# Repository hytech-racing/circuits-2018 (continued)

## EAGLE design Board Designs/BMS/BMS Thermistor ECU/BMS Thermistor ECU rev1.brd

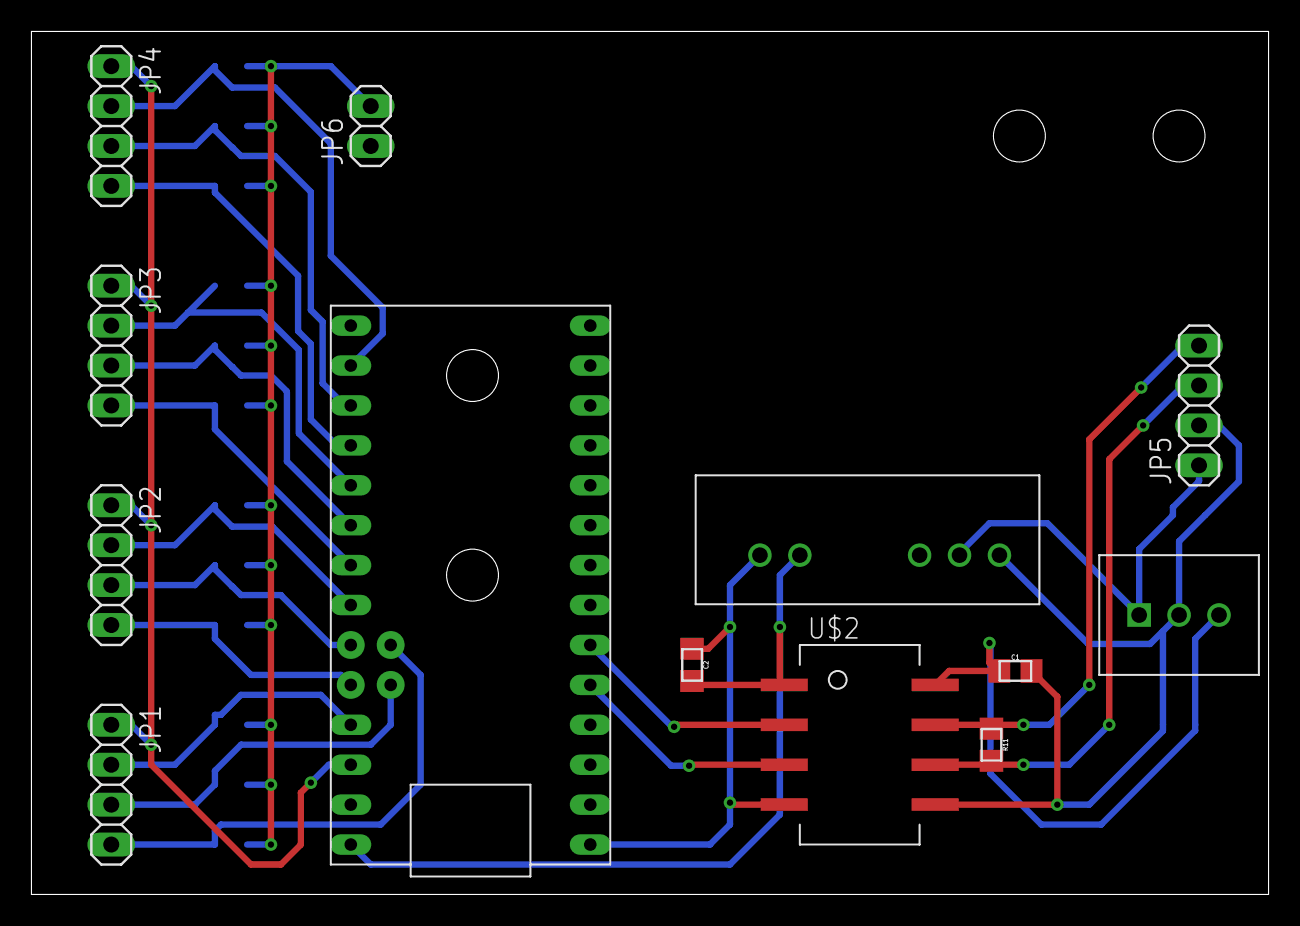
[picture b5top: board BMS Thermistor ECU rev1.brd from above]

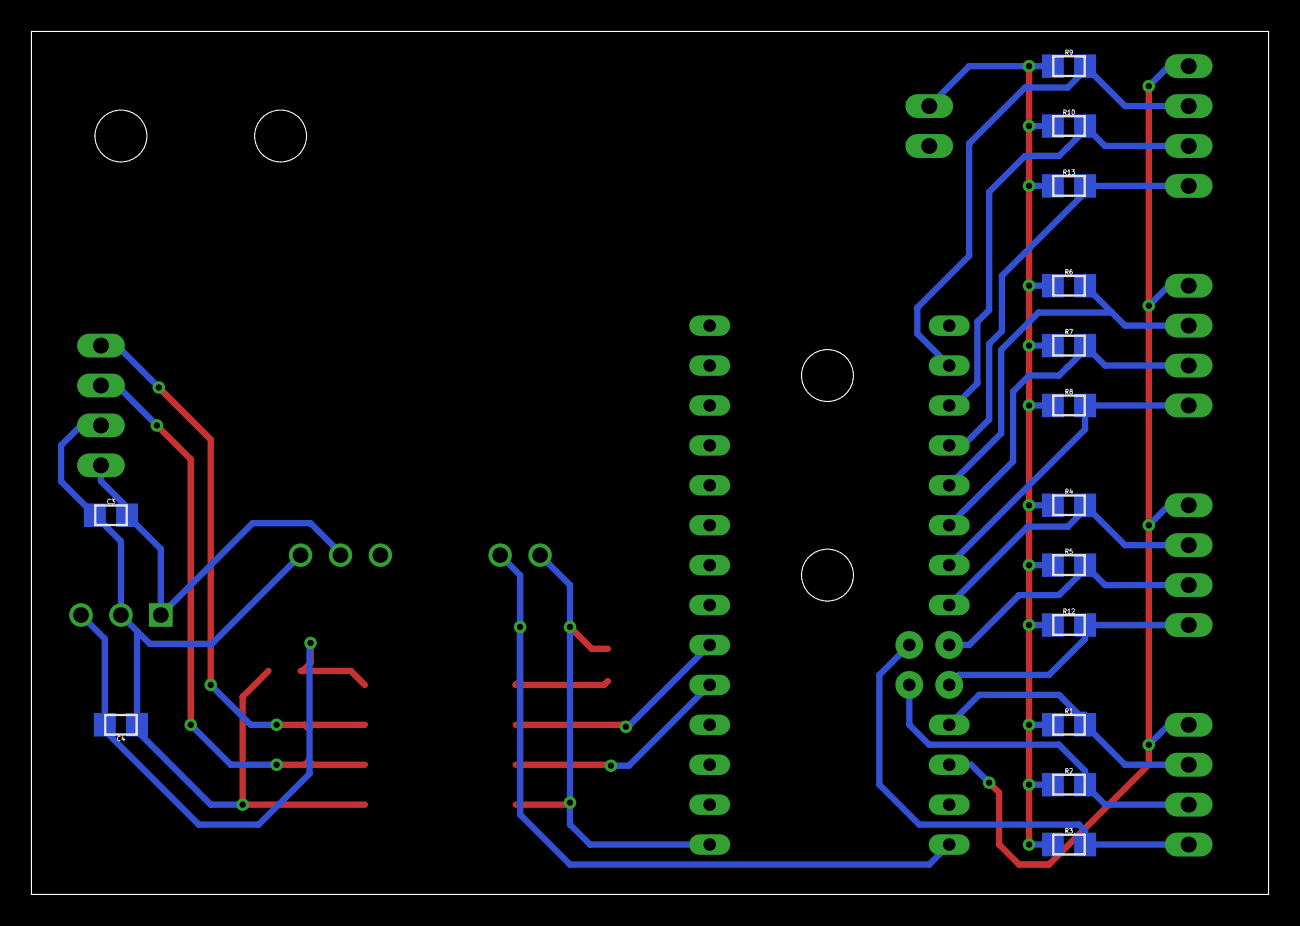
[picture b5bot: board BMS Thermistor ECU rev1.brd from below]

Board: 2 copper layers, 78.7 x 54.9 mm, 27 parts (14 on the bottom side), 23 nets.

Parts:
C1, C2, C4: 0.1u; 0805
C3: 0.33u; 0805
IC1: TO-220-SPACED
JP1, JP2, JP3, JP4, JP5: 1X04
JP6: M02; 1X02
R1, R2, R3, R4, R5, R6, R7, R8, R9, R10, R12, R13: 0805
R11: 120; 0805
U$1: TEENSY_3.2_12ANALOG
U$2: ISO1050CAN; DUB8
U$3: NCS1S1205SC-12V-5VCONVERTER; DCDC-CONVERTER

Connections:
3.3V: JP1.1, JP2.1, JP3.1, JP4.1, U$1.3.3V
unnamed: C1.2, C3.1, C4.1, IC1.2, JP5.2, U$2.P$5, U$3.-VIN
unnamed: JP3.3, R7.2, U$1.A4
unnamed: JP3.4, R8.2, U$1.A5
unnamed: C3.2, IC1.1, JP5.1, U$3.+VIN
unnamed: C1.1, C4.2, IC1.3, U$2.P$8
unnamed: JP5.4, R11.1, U$2.P$7
unnamed: JP5.3, R11.2, U$2.P$6
unnamed: U$1.D3(CANTX), U$2.P$3
unnamed: U$1.D4(CANRX), U$2.P$2
unnamed: C2.2, U$1.VIN, U$2.P$1, U$3.+VOUT
unnamed: C2.1, U$1.GND, U$2.P$4, U$3.-VOUT
unnamed: JP2.4, R12.2, U$1.A8
unnamed: JP4.4, R13.2, U$1.A2
THERM1: JP1.2, R1.2, U$1.A9
THERM2: JP1.3, R2.2, U$1.A10
THERM3: JP1.4, R3.2, U$1.A11
THERM4: JP2.2, R4.2, U$1.A6
THERM5: JP2.3, R5.2, U$1.A7
THERM6: JP3.2, R6.2, U$1.A3
THERM9: JP4.2, R9.2, U$1.A0
THERM10: JP4.3, R10.2, U$1.A1
TS_GND: JP6.2, R1.1, R2.1, R3.1, R4.1, R5.1, R6.1, R7.1, R8.1, R9.1, R10.1, R12.1, R13.1
